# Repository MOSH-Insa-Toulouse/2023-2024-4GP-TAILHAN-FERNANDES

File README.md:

# 2023-2024-4GP-TAILHAN-FERNANDES
# Projet capteur avec jauge de contrainte de graphène
## Description générale : 
  Nous sommes Amandine Tailhan et David Fernandes, deux élèves de l'INSA Toulouse. Dans le cadre de notre quatrième année, nous avons entrepris un projet sur les capteurs. Notre objectif principal était de déterminer les caractéristiques principales d'une jauge de contrainte low-tech et de les comparer avec sa version conventionnelle, qualifiée de "high-tech". Ce projet vise à répondre à la question suivante : *"Ne pourrait-on pas obtenir parfois les mêmes résultats avec une technologie low-tech qu'avec une technologie high-tech ?"*
<br> <br>
Pour réaliser cette comparaison, nous avons conçu un banc de test à partir de zéro. Sur ce dépôt GitHub, vous trouverez tous les outils et codes que nous avons développés pour répondre à cette question. Enfin, à la fin de ce dépôt, vous découvrirez la réponse à notre problématique.

## Contenu : 
Dans ce github vous retrouverez tout le travail réalisé dans le contexte de ce projet capteur. Vous trouverez un dossier indépendant pour chaque partie de notre projet. <br> <br>
**1. Code Arduino :** Vous trouverez un dossier appelé Arduino dans lequel se trouvent les différents codes arduinos qui pilotent de manière indépendante chacun des composants de notre banc de test et un code appelé "Assemblage_composants" qui pilote l'ensemble de notre banc de test. Dans chaque sous-dossier vous trouverez un schémas des branchements. <br>
**2. Shield dans KiCAD :** Dans le dossier KiCAD  vous trouverez le schéma du montage avec les différents branchements correspondant à notre banc de test : . Vous trouverez également le fichier .pcb que vous pourrez utiliser si vous voulez commander le PCB. La réalisation du PCB permet un meilleur agencement des composants ajoutant ainsi un confort d'utilisation. Cependant, le montage pourra également être réalisé avec des breadboards et des branchements "à la main". <br>
**3. Impression 3D du support:** Notre banc de test utilise un support où l'on vient installer la jauge de contrainte à tester et le servo moteur qui nous servira à appliquer la contrainte sur le capteur. Dans ce dossier vous trouverez le modèle 3D de cette pièce (réalisé sur la version étudiant 10 de PTC Creo) ainsi que le fichier .stl qui vous permettra d'imprimer la pièce avec une imprimante 3D. Cette étape n'est pas obligatoire, vous pouvez très bien réaliser un support pour le capteur et le servo moteur chez vous et ainsi faire votre propre banc de test. <br> 
**4. L'application bluetooth :** À l'aide du logiciel MIT App Inventor nous avons également réalisé une application compatible avec n'importe quel téléphone Android. Cette application permet la communication entre votre smartphone Android et le circuit. Vous pourrez dans cette application visualiser les courbes de contraintes du capteur que vous étudiez. <br>
**5. Datasheet du capteur Low Tech :** Dans le dossier datasheet, vous aurez accès aux informations techniques importantes relatives au capteur. Cela inclut la sensibilité du capteur de graphite pour divers types de crayons tels que F, HB, B, 2B et 4B. Vous y trouverez également des graphiques détaillant la variation relative de résistance en fonction de la déformation selon l'axe z en situation de tension et de compression.
**6. Présentation finale de notre projet :** Vous trouverez parmi les dépôts un document PowerPoint intitulé "Présentation_projet.pptx". Dans ce PowerPoint, nous présentons notre démarche, les différentes étapes du projet, ainsi que des images et une vidéo illustrant le résultat final de notre projet. Cette vidéo pourra vous aider à mieux comprendre et à mieux visualiser l'assemblage de toutes les pièces, c'est pourquoi nous vous invitons à y jeter un œil.

## Pré-requis : 
- Application Arduino, version : >2.1
- Arduino UNO
- Librairies Arduino : Adafruit_SSD1306.h / SPI.h / Servo.h / SoftwareSerial.h
- Smartphone Android (si vous voulez visualiser les courbes de contraintes sur votre smartphone)
- Imprimante 3D (Si vous voulez imprimer le support qu'on propose si vous ne voulez pas faire vous-même le banc de test)
- Commander le PCB (optionnel), sinon 2 breadboards et des fils suffiront 
- Capteur Bluetooth HC05 
- Servo-moteur SM-S2309S
- Encodeur rotatoire KY 040
- Potentiomètre digital MCP 4 1050
- OLED 2864
- Amplificateur opérationnel : LTC1050
- Résistances et condensateurs : voir schémas 

## Guide d'utilisation : 
### Montage :
1. Le premier pas, avant de démarrer, sera de réaliser le montage présenté ci-dessous : 
2. Nous vous recommandons fortement que vous installiez les composants un par un et que vous les testiez individuellement avec les programmes fournis dans /Arduino

1. Une fois les branchements effectués : brancher l'arduino UNO à votre PC 
2. Ouvrez le fichier assemblage.ino qui se trouve dans /Arduino/Assemblage
3. Sélectionnez votre Arduino UNO une fois le programme ouvert 
4. Lancez le code 

### Menu sur l'OLED : 
  Lorsque vous lancez le code sur l'Arduino l'écran OLED s'allume. Sur l'écran OLED vous pourrez accéder à deux menus différents. Le premier menu permet de choisir quelle jauge de contrainte vous voulez mesurer : celle en graphène et la conventionnelle. Le deuxième menu affiche la valeur de la résistance R2 et l'option de recalibration de celle-ci. En effet, en fonction du crayon utilisée pour faire le capteur de graphène la résistance à l'état de repos peut être plus ou moins grande c'est pour celà qu'on a ajouté l'option de recalibration qui permet d'ajuster le gain du montage en modifiant la valeur de la résistance R2. <br> <br>
Pour passer d'un menu à un autre il faut appuyer sur l'encodeur rotatoire. À l'intérieur de chaque menu pour se déplacer parmis les différentes options vous n'avez qu'à faire tourner l'encodeur. Ainsi pour mesurer la résistance de la jauge de contrainte en graphène il faut se placer dans le menu "Résistances" et sélectionner la résistance R graph. D'autre part, pour réaliser la calibration de la résistance R2 il faut se placer dans le menu "Calibration", sélectionner l'option "Recalibration" et appuyer sur l'encodeur 2s.

### Application :

1. Appariez votre smartphone avec votre module Bluetooth HC05. Si un code est demandé, tapez soit 0000 soit 1234.
2. Téléchargez le fichier .exe sur votre smartphone en scannant le QR Code que vous trouverez dans le dossier /Application Android.
3. Une fois l'application installée sur votre Android, accordez les droits nécessaires à votre application afin qu'elle puisse détecter les appareils Bluetooth connectés à votre Android via les paramètres.
4. Ouvrez l'application sur votre smartphone, puis cliquez sur le logo Connect + Bluetooth.
5. Sélectionnez le module HC05.
6. Normalement, la courbe de contrainte de votre capteur s'affiche.
7. Pour afficher la bonne courbe, vous devez introduire manuellement la valeur de R2 (lue sur l'écran OLED, menu : Calibration), puis cliquez sur le bouton "Actualiser R2" de l'application.
8. L'application vous permet également d'arrêter ou de lancer la rotation du servo-moteur avec les boutons : Moteur ON / Moteur OFF.

### Banc de test :

Veuillez trouver ci-dessous une image de notre banc de test : 

<br> <br>
Au centre, vous pouvez observer la pièce principale qui jouera le rôle de support pour notre banc d'essai. À sa droite est positionné le servo-moteur, accompagné du capteur de graphite. À gauche, se trouve l'Arduino UNO et juste au-dessus de celui-ci s'étend notre montage électrique intégré dans le PCB.

Pour réaliser ce banc de test, suivez les étapes suivantes :

#### Support :
1. Vissez l'Arduino UNO sur le support.
2. Réalisez le PCB.
3. Effectuez toutes les soudures nécessaires.
4. Installez le PCB sur l'Arduino. (L'étape de 2 à 4 peut être remplacée par l'utilisation d'un breadboard et de câbles.)
5. Placez le servo-moteur ; les fils du servo-moteur sont à droite du support.
6. Vissez les deux pinces du capteur à gauche du servo-moteur.
7. Sur les "bras" du servo-moteur, vissez un bras suffisamment long pour atteindre le capteur de graphite (4-5cm).
    - Éteignez l'alimentation du servo-moteur.
    - Tournez ses bras dans le sens opposé des aiguilles d'une montre jusqu'au maximum.
    - Maintenant, enlevez le "bras" du servo-moteur et ajustez-le de manière à ce qu'il fasse un angle compris entre -50 et -20 degrés par rapport à l'axe horizontal.
    - Mesurez cet angle et rentrez-le dans le code Arduino dans la variable : angle_min.
    - Ajustez la variable angle_max de manière à ce que le bras du servo-moteur dépasse le capteur.

#### Acquisition de données :
1. Après vérification que tout fonctionne convenablement, fermez le logiciel Arduino (en mémorisant le port sur lequel votre Arduino UNO est connecté).
2. Dans le dossier /Acquisition_donnees, créez un document vide .txt.
3. Ouvrez le code python "enregistrement_donnees.py" que vous trouverez dans : /Acquisition_donnees.
4. Changez le chemin du fichier par le chemin du fichier .txt que vous avez créé.
5. Lancez le code python.
6. Laissez le code tourner jusqu'à la fin.
7. Les données sont normalement stockées dans le fichier .txt (ATTENTION : notez les valeurs de n pour lesquelles le capteur est au repos).

#### Traitement de données :
1. Ouvrez les fichiers .txt avec Excel en choisissant "," comme séparateur de colonne.
2. Effacez toutes les lignes pour lesquelles le capteur est au repos.
3. Ordonnez votre tableau par déformation_z_cm croissante.
4. Enregistrez les données dans le tableau/feuille qui vous paraît pertinent, dans le fichier donnees_courbes.
5. Les courbes sont automatiquement générées dans la feuille : Ensemble.

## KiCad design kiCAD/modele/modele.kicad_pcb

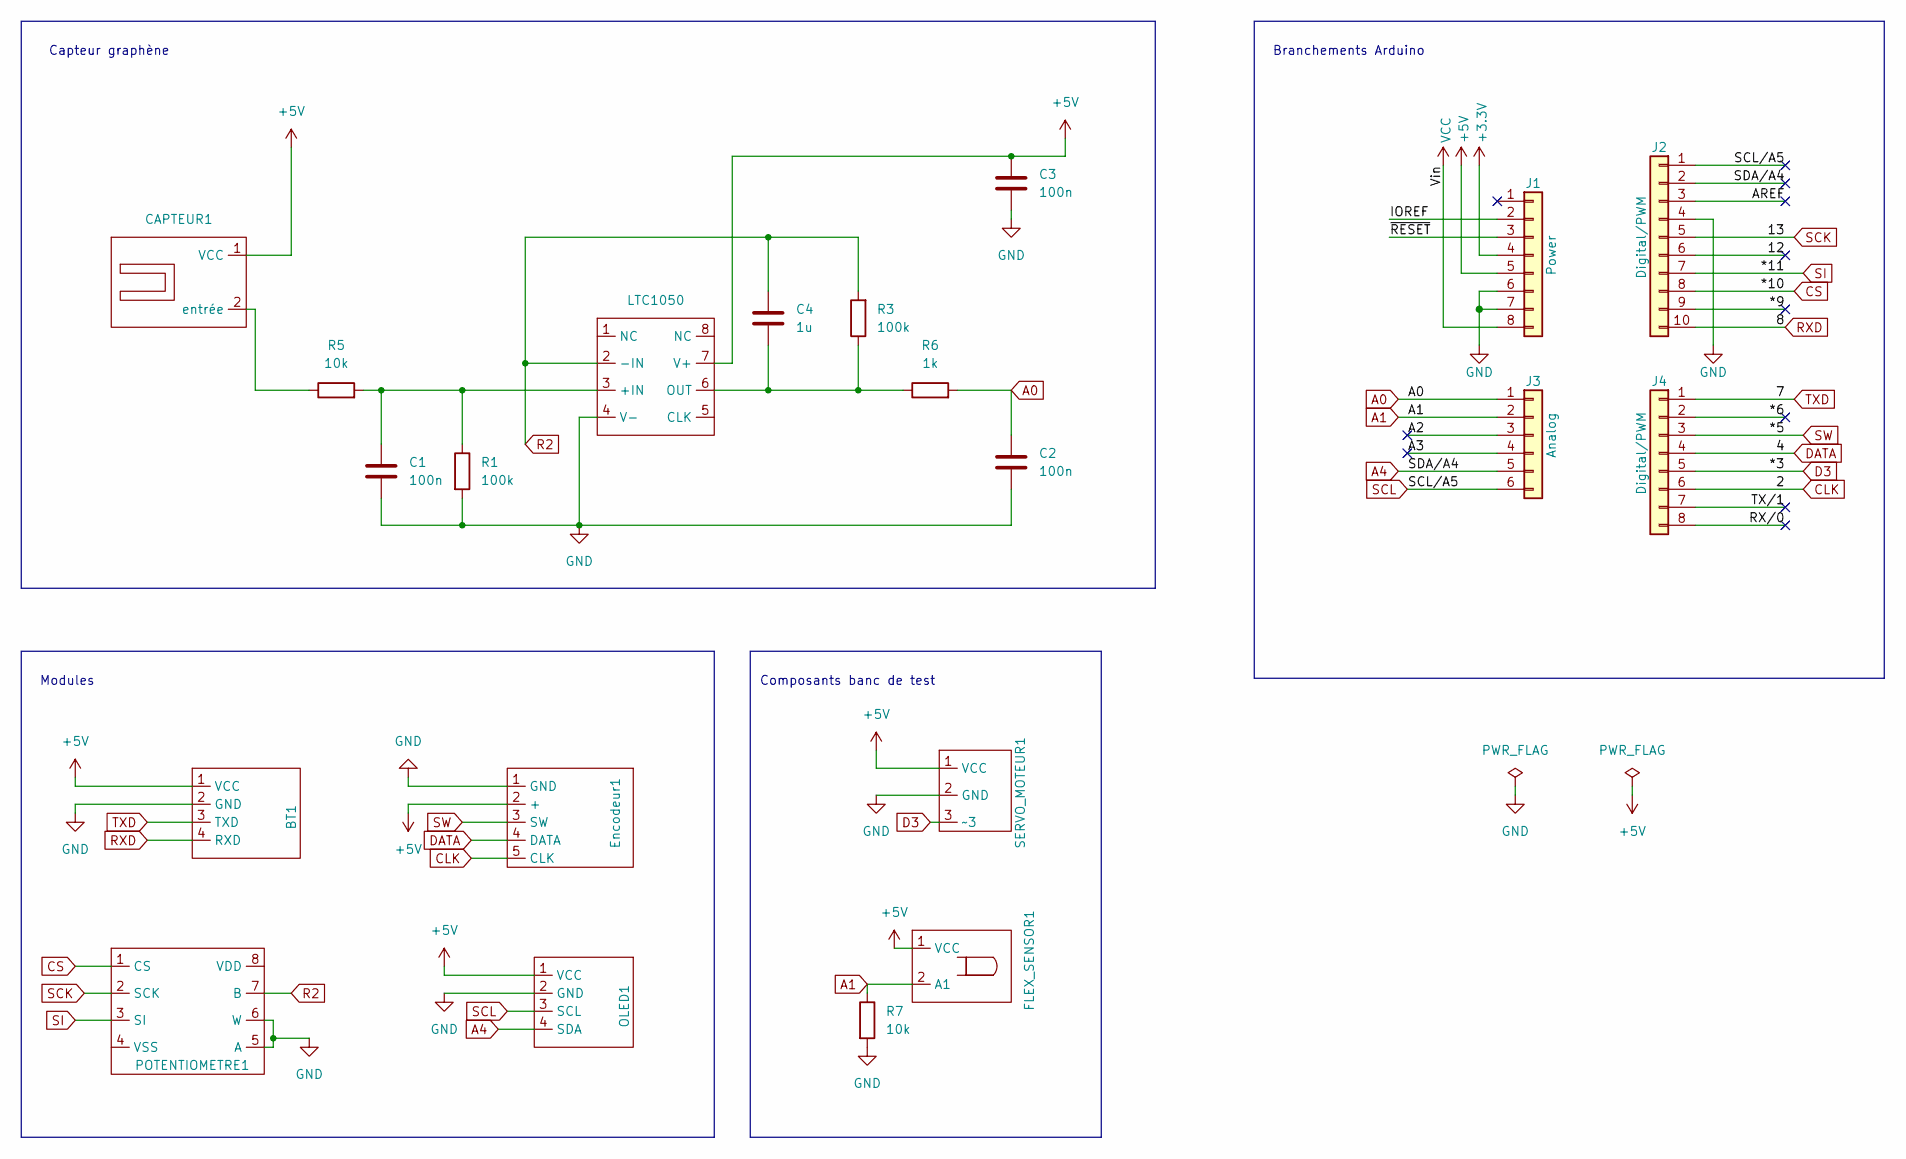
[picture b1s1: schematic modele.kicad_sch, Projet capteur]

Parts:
BT1: BT
C1, C2, C3: 100n; C_Disc_D4.3mm_W1.9mm_P5.00mm
C4: 1u; C_Rect_L7.0mm_W3.5mm_P5.00mm
CAPTEUR1: capteur
Encodeur1: Encoder KY-040
FLEX_SENSOR1: Flex_Sensor
J1: Power; PinSocket_1x08_P2.54mm_Vertical
J2: Digital/PWM; PinSocket_1x10_P2.54mm_Vertical
J3: Analog; PinSocket_1x06_P2.54mm_Vertical
J4: Digital/PWM; PinSocket_1x08_P2.54mm_Vertical
LTC1050: AOP-LTC1050
OLED1: OLED-2864
POTENTIOMETRE1: MCP41050
R1, R3: 100k; R_Axial_DIN0204_L3.6mm_D1.6mm_P5.08mm_Horizontal
R5, R7: 10k; R_Axial_DIN0204_L3.6mm_D1.6mm_P5.08mm_Horizontal
R6: 1k; R_Axial_DIN0207_L6.3mm_D2.5mm_P7.62mm_Horizontal
SERVO_MOTEUR1: Servo_moteur

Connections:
+3V3: J1.4
+5V: BT1.1 (VCC), C3.1, CAPTEUR1.1 (VCC), Encodeur1.2 (+), FLEX_SENSOR1.1 (VCC), J1.5, LTC1050.7 (V+), OLED1.1 (VCC), SERVO_MOTEUR1.1 (VCC)
/12: J2.6
/*6: J4.2
/*9: J2.9
/A2: J3.3
/A3: J3.4
/AREF: J2.3
/IOREF: J1.2
/RX/0: J4.8
/TX/1: J4.7
/~RESET: J1.3
A0: C2.1, J3.1, R6.2
A1: FLEX_SENSOR1.2 (A1), J3.2, R7.1
A4: J2.2, J3.5, OLED1.4 (SDA)
CLK: Encodeur1.5 (CLK), J4.6
CS: J2.8, POTENTIOMETRE1.1 (CS)
D3: J4.5, SERVO_MOTEUR1.3 (~3)
DATA: Encodeur1.4 (DATA), J4.4
GND: BT1.2 (GND), C1.2, C2.2, C3.2, Encodeur1.1 (GND), J1.6, J1.7, J2.4, LTC1050.4 (V-), OLED1.2 (GND), POTENTIOMETRE1.5 (A), POTENTIOMETRE1.6 (W), R1.2, R7.2, SERVO_MOTEUR1.2 (GND)
unnamed: CAPTEUR1.2 (entrée), R5.1
unnamed: C1.1, LTC1050.3 (+IN), R1.1, R5.2
unnamed: C4.2, LTC1050.6 (OUT), R3.1, R6.1
R2: C4.1, LTC1050.2 (-IN), POTENTIOMETRE1.7 (B), R3.2
RXD: BT1.4 (RXD), J2.10
SCK: J2.5, POTENTIOMETRE1.2 (SCK)
SCL: J2.1, J3.6, OLED1.3 (SCL)
SI: J2.7, POTENTIOMETRE1.3 (SI)
SW: Encodeur1.3 (SW), J4.3
TXD: BT1.3 (TXD), J4.1
VCC: J1.8

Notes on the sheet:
Capteur graphène
Modules
Composants banc de test
Branchements Arduino

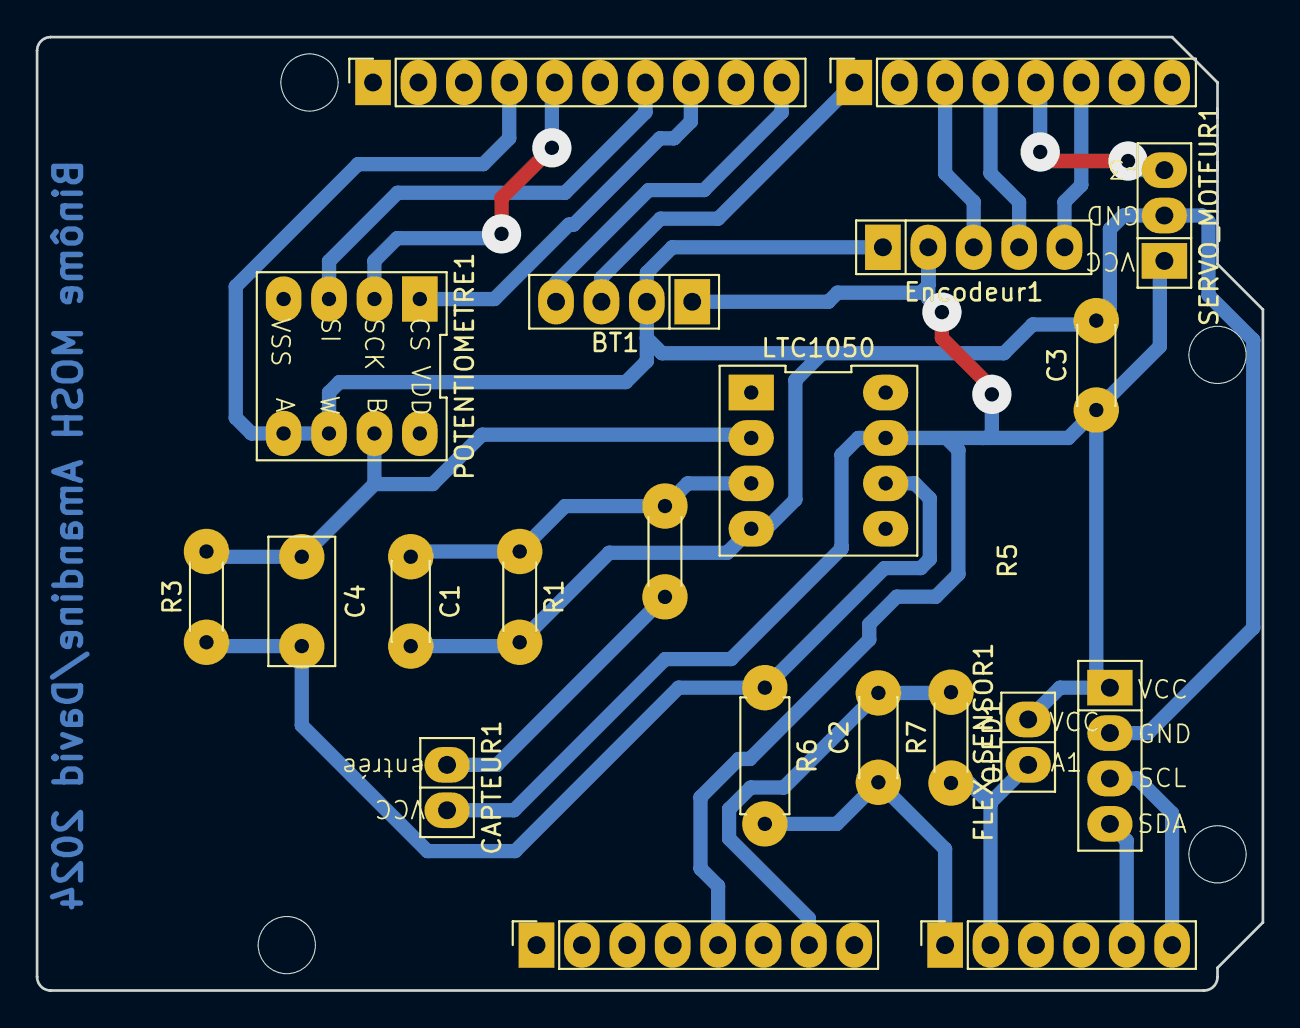
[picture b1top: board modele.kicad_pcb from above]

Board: 2 copper layers, 68.6 x 53.3 mm, 25 parts (0 on the bottom side), 19 nets.

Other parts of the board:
MH1, MH2, MH3, MH4: MountingHole_3.2mm

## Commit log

2024-03-07 ajout text.txt
2024-03-07 modification texte
2024-03-07 modification nom du fichier texte
2024-05-17 Add files via upload
    Addition de la data excel des courbe déformation
2024-05-17 Add files via upload
    Bon dossier d'acquisition des donnees
2024-05-17 Add files via upload
    Addition des dossiers
2024-05-17 Supprimer le dossier Ensembles_donnees
2024-05-17 Add files via upload
    Addition de dossier KiCAD
2024-05-17 Ajout description présentation
    Ajout description présentation
2024-05-17 Addition de dossier avec programmes arduino
2024-05-17 Addition Datasheet
2024-05-17 Addition images pcb
2024-05-17 ajout image montage readme
2024-05-17 ajout image banc test readme
